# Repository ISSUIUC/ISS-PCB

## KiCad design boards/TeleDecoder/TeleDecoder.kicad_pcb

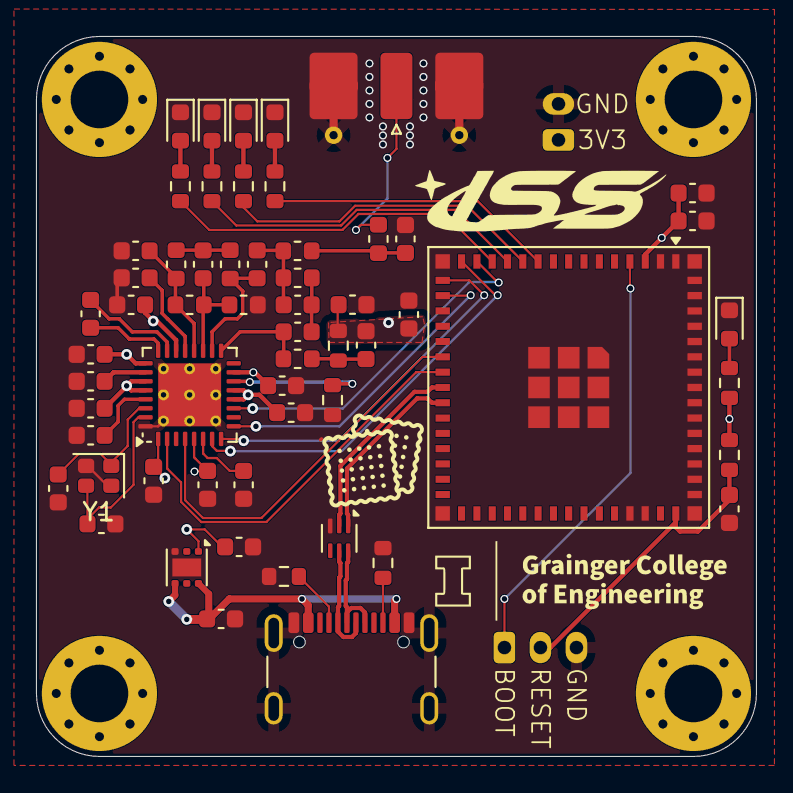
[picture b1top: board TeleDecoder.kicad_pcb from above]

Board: 4 copper layers, 40.0 x 40.0 mm, 64 parts (0 on the bottom side), 44 nets.

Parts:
C1, C2, C127: 1uF; C_0603_1608Metric
C101: 22uF; C_0603_1608Metric
C102: 100nF; C_0603_1608Metric
C103, C119: 10nF; C_0603_1608Metric
C104: 56pF; C_0603_1608Metric
C105: 100pF; C_0603_1608Metric
C106: 39pF; C_0603_1608Metric
C107: 2.2pF; C_0603_1608Metric
C108, C109: 10pF; C_0603_1608Metric
C110, C111, C113: 5.1pF; C_0603_1608Metric
C112: 1.8nF; C_0603_1608Metric
C114: 6.2pF; C_0603_1608Metric
C115, C117, C118, C120, C121, C122, C123, C124, C125: 47nF; C_0603_1608Metric
C116: 220nF; C_0603_1608Metric
D101, D105: LED_RED; LED_0603_1608Metric
D102: LED_BLUE; LED_0603_1608Metric
D103: LED_GREEN; LED_0603_1608Metric
D104: LED_ORANGE; LED_0603_1608Metric
H101, H102, H103, H104: MountingHole; MountingHole_3.2mm_M3_Pad_Via
J101: Conn_01x03; JST_PH_B3B-PH-K_1x03_P2.00mm_Vertical
J102: USB4105-GF-A; USB_C_Receptacle_GCT_USB4105-xx-A_16P_TopMnt_Horizontal
J103: Conn_01x02; JST_PH_B2B-PH-K_1x02_P2.00mm_Vertical
J104: Conn_Coaxial; SMA_Molex_73251-2120_EdgeMount_Horizontal
L101, L102: 56nH; L_0603_1608Metric
L103, L106: 15nH; L_0603_1608Metric
L104, L105: 27nH; L_0603_1608Metric
L107: 43nH; L_0603_1608Metric
L108: 22nH; L_0603_1608Metric
R101, R102: 5.1k; R_0603_1608Metric
R103: 18; R_0603_1608Metric
R104: 56k; R_0603_1608Metric
R105, R106, R107, R108, R110: 470; R_0603_1608Metric
R109: 20k; R_0603_1608Metric
U101: ESP32-S3-MINI-1U; ESP32-S2-MINI-1U
U102: ECMF02-2AMX6; ST_UQFN-6L_1.5x1.7mm_P0.5mm
U103: CC1120; VQFN-32-1EP_5x5mm_P0.5mm_EP3.5x3.5mm_ThermalVias
U104: TPS746-Q1; WSON-6-1EP_2x2mm_P0.65mm_EP1x1.6mm
Y1: STDCZS3-40M; Crystal_SMD_2016-4Pin_2.0x1.6mm

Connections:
+3V3: C2.1, C101.1, C102.1, C103.1, C104.2, C105.1, C115.1, C117.1, C118.1, C120.1, C121.1, C123.1, C124.1, J103.1, R103.2, R109.2, R110.1, U101.3 (3V3), U103.1 (VDD_GUARD), U103.5 (DVDD), U103.12 (DVDD), U103.13 (AVDD_IF), U103.15 (AVDD_RF), U103.22 (AVDD_SYNTH1), U103.25 (AVDD_PFD_CHP), U103.27 (AVDD_SYNTH2), U103.28 (AVDD_XOSC), U104.1 (OUT)
+5V: C1.1, J102.A4 (VBUS), J102.A9 (VBUS), J102.B4 (VBUS), J102.B9 (VBUS), U104.4 (EN), U104.6 (IN)
/BOOT: J101.1, U101.4 (IO0)
/CS_RADIO: U101.14 (IO10), U103.11 (~CS)
/D+: J102.A6 (D+), J102.B6 (D+), U102.6 (D+_out)
/D-: J102.A7 (D-), J102.B7 (D-), U102.5 (D-_out)
/LED_BLUE: R106.1, U101.13 (IO9)
/LED_GREEN: R107.1, U101.12 (IO8)
/LED_ORANGE: R108.1, U101.11 (IO7)
/LED_RED: R105.1, U101.10 (IO6)
/LNA_N: C111.1, L102.2, L105.1, U103.20 (LNA_N)
/LNA_P: C110.1, L102.1, L104.1, U103.19 (LNA_P)
/MISO0: U101.17 (IO13), U103.9 (SO(GPIO1))
/MOSI0: U101.15 (IO11), U103.7 (SI)
/PA: C106.1, L101.1, U103.17 (PA)
/RADIO_INT: U101.21 (IO17), U103.4 (GPIO2)
/RESET: C127.1, J101.2, R109.1, U101.45 (EN)
/SCLK0: U101.16 (IO12), U103.8 (SCLK)
/TRX_SW: C113.1, L106.1, U103.18 (TRX_SW)
/USB_D+: U101.24 (USB_D+), U102.1 (D+_in)
/USB_D-: U101.23 (USB_D-), U102.2 (D-_in)
GND: C1.2, C2.2, C101.2, C102.2, C103.2, C105.2, C108.2, C109.2, C111.2, C114.2, C115.2, C116.2, C117.2, C118.2, C119.2, C120.2, C121.2, C122.2, C123.2, C124.2, C125.2, C127.2, D101.1 (K), D102.1 (K), D103.1 (K), D104.1 (K), D105.1 (K), J101.3, J102.A1 (GND), J102.A12 (GND), J102.B1 (GND), J102.B12 (GND), J102.S1 (SHIELD), J103.2, J104.2 (Ext), L104.2, R101.2, R102.2, R104.2, U101.1 (GND), U101.2 (GND), U101.42 (GND), U101.43 (GND), U101.46 (GND), U101.47 (GND), U101.48 (GND), U101.49 (GND), U101.50 (GND), U101.51 (GND), U101.52 (GND), U101.53 (GND), U101.54 (GND), U101.55 (GND), U101.56 (GND), U101.57 (GND), U101.58 (GND), U101.59 (GND), U101.60 (GND), U101.61 (GND), U101.62 (GND), U101.63 (GND), U101.64 (GND), U101.65 (GND), U102.3 (GND), U103.32 (EXT_XOSC), U103.33 (GND_EP), U104.3 (GND), U104.7 (EP), Y1.2
unnamed: C104.1, L101.2, R103.1
unnamed: C106.2, C107.1, L103.1
unnamed: C107.2, C113.2, L103.2, L107.1
unnamed: C110.2, L105.2, L106.2
unnamed: C114.1, L107.2, L108.1
unnamed: D101.2 (A), R105.2
unnamed: D102.2 (A), R106.2
unnamed: D103.2 (A), R107.2
unnamed: D104.2 (A), R108.2
unnamed: D105.2 (A), R110.2
unnamed: J102.A5 (CC1), R101.1
unnamed: J102.B5 (CC2), R102.1
unnamed: J104.1 (In), L108.2
unnamed: C116.1, U103.6 (DCPL)
unnamed: C122.1, U103.26 (DCPL_PFD_CHP)
unnamed: C119.1, U103.21 (DCPL_VCO)
unnamed: C125.1, U103.29 (DCPL_XOSC)
unnamed: C112.1, U103.23 (LPF0)
unnamed: C112.2, U103.24 (LPF1)
unnamed: R104.1, U103.14 (RBIAS)
unnamed: C108.1, U103.30 (XOSC_Q1), Y1.1
unnamed: C109.1, U103.31 (XOSC_Q2), Y1.3

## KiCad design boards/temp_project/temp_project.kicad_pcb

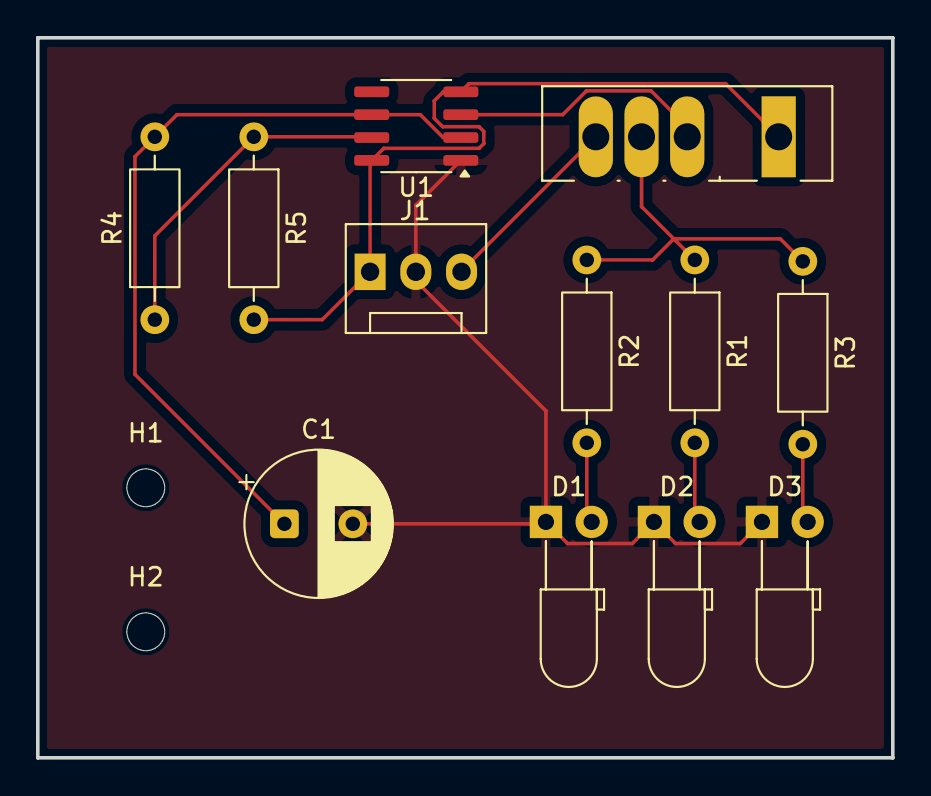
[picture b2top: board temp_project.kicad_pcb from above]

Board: 2 copper layers, 47.5 x 40.0 mm, 14 parts (0 on the bottom side), 9 nets.

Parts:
C1: C_Polarized; CP_Radial_D8.0mm_P3.80mm
D1: RED; LED_D3.0mm_Horizontal_O3.81mm_Z6.0mm
D2: BLUE; LED_D3.0mm_Horizontal_O3.81mm_Z6.0mm
D3: GREEN; LED_D3.0mm_Horizontal_O3.81mm_Z6.0mm
H1, H2: MountingHole; MountingHole_2.1mm
J1: Conn_01x02; FanPinHeader_1x03_P2.54mm_Vertical
Q1: NMOS; TO-247-4_Vertical
R1, R2, R3: 500; R_Axial_DIN0207_L6.3mm_D2.5mm_P10.16mm_Horizontal
R4, R5: 50k; R_Axial_DIN0207_L6.3mm_D2.5mm_P10.16mm_Horizontal
U1: LM555xM; SOIC-8_3.9x4.9mm_P1.27mm

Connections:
+9V: J1.1, Q1.1 (D), R5.2, U1.4 (R), U1.8 (VCC)
/THR: C1.1, R4.2, U1.2 (TR), U1.6 (THR)
GND: C1.2, D1.1 (K), D2.1 (K), D3.1 (K), J1.2, U1.1 (GND)
unnamed: D1.2 (A), R2.2
unnamed: D2.2 (A), R1.2
unnamed: D3.2 (A), R3.2
unnamed: Q1.2 (G), U1.3 (Q)
unnamed: Q1.3 (S), R1.1, R2.1, R3.1
unnamed: R4.1, R5.1, U1.7 (DIS)
